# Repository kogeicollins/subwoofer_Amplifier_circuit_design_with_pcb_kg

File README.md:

# subwoofer_Amplifier_circuit_design_with_pcb_kg
 circuit and pcb of a subwoofer amplifier

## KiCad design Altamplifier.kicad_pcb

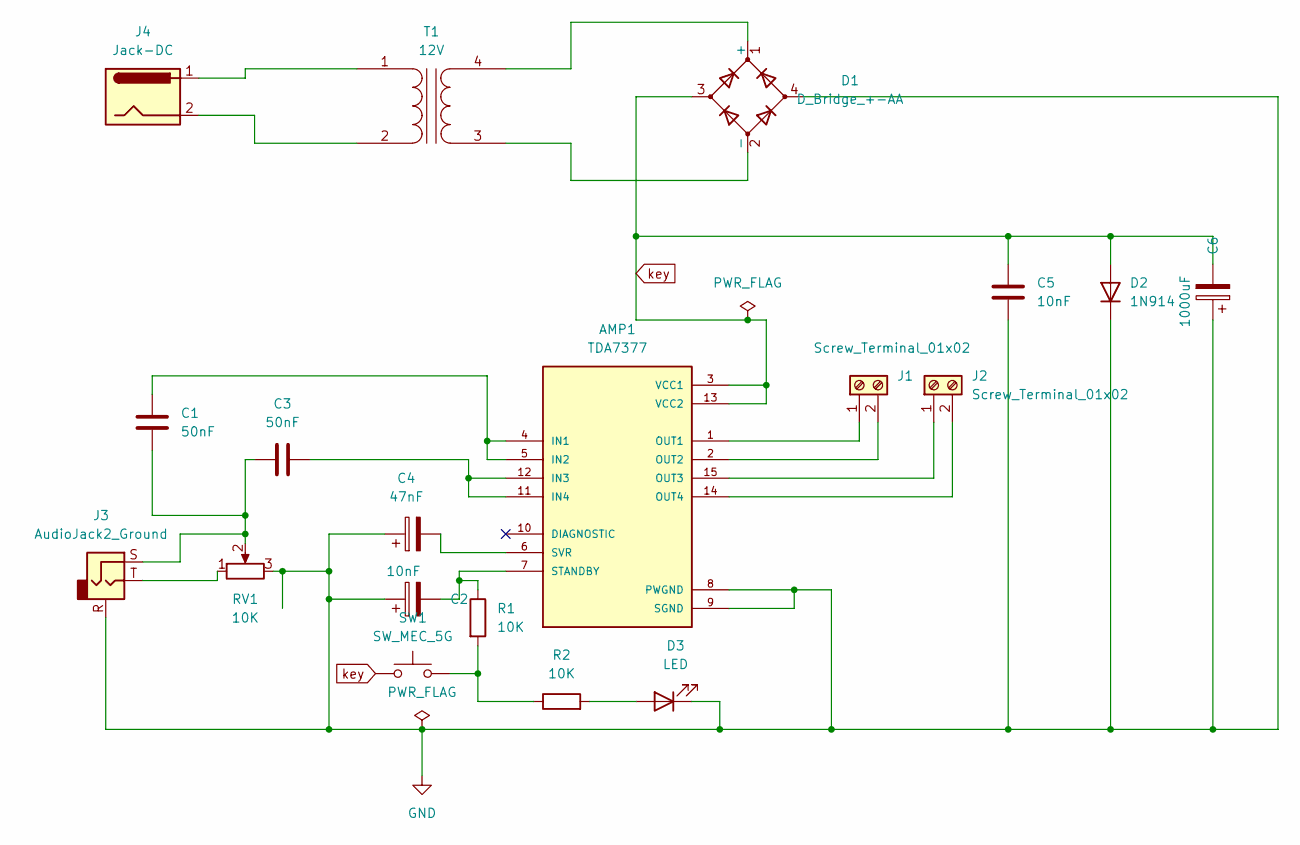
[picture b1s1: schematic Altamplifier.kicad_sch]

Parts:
AMP1: TDA7377; AMP_TDA7377
C1: 50nF; C_Rect_L9.0mm_W3.9mm_P7.50mm_MKT
C2: 10nF; CP_Elec_6.3x4.5
C3: 50nF; CP_Elec_6.3x4.5
C4: 47nF; CP_Elec_6.3x4.5
C5: 10nF; C_Rect_L9.0mm_W3.9mm_P7.50mm_MKT
C6: 1000uF; CP_Elec_6.3x5.4
D1: D_Bridge_+-AA; Diode_Bridge_Bourns_CD-DF4xxS
D2: 1N914; D_DO-35_SOD27_P7.62mm_Horizontal
D3: LED; LED_D3.0mm_Horizontal_O3.81mm_Z6.0mm
J1, J2: Screw_Terminal_01x02; JST_JWPF_B02B-JWPF-SK-R_1x02_P2.00mm_Vertical
J3: AudioJack2_Ground; Jack_3.5mm_CUI_SJ1-3533NG_Horizontal
J4: Jack-DC; BarrelJack_SwitchcraftConxall_RAPC10U_Horizontal
R1, R2: 10K; R_0201_0603Metric_Pad0.64x0.40mm_HandSolder
RV1: 10K; Potentiometer_Bourns_3214X_Vertical
SW1: SW_MEC_5G; SW_MEC_5GSH9
T1: 12V; Transformer_Toroid_Horizontal_D10.5mm_Amidon-T37

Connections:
GND: AMP1.8 (PWGND), AMP1.9 (SGND), C2.1, C4.1, C5.2, C6.1, D1.4, D2.1 (K), D3.1 (K), J3.R, RV1.3
unnamed: AMP1.4 (IN1), AMP1.5 (IN2), C1.1
unnamed: AMP1.11 (IN4), AMP1.12 (IN3), C3.2
unnamed: AMP1.1 (OUT1), J1.1
unnamed: AMP1.2 (OUT2), J1.2
unnamed: AMP1.15 (OUT3), J2.1
unnamed: AMP1.14 (OUT4), J2.2
unnamed: AMP1.7 (STANDBY), C2.2, R1.1
unnamed: AMP1.6 (SVR), C4.2
unnamed: C1.2, C3.1, J3.S, RV1.2
unnamed: D1.1 (+), T1.4 (SB)
unnamed: D1.2 (-), T1.3 (SA)
unnamed: D3.2 (A), R2.2
unnamed: J3.T, RV1.1
unnamed: R1.2, R2.1, SW1.3 (B), SW1.4 (B)
unnamed: J4.1, T1.1 (AA)
unnamed: J4.2, T1.2 (AB)
key: AMP1.3 (VCC1), AMP1.13 (VCC2), C5.1, C6.2, D1.3, D2.2 (A), SW1.1 (A), SW1.2 (A)

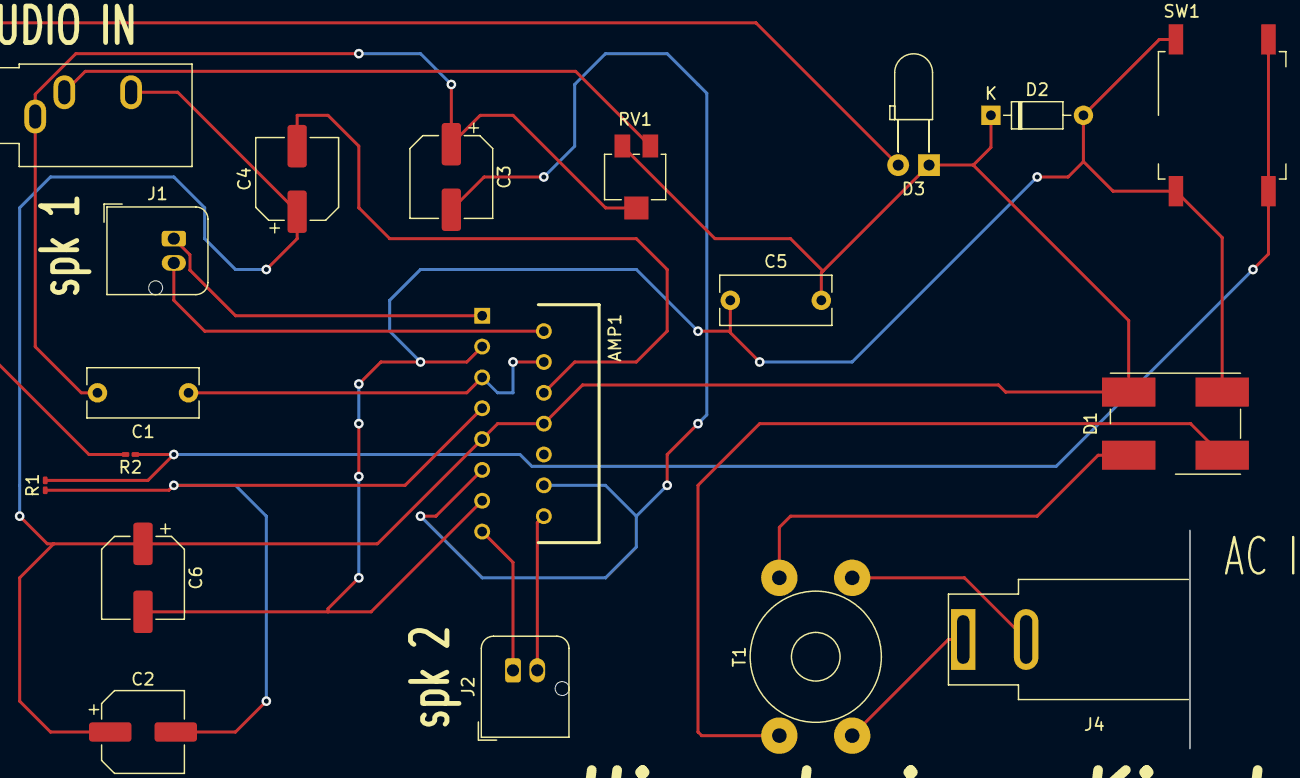
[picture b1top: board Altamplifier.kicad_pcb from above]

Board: 2 copper layers, 19 parts (0 on the bottom side), 18 nets.

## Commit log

2024-11-27 the files
    first commit
